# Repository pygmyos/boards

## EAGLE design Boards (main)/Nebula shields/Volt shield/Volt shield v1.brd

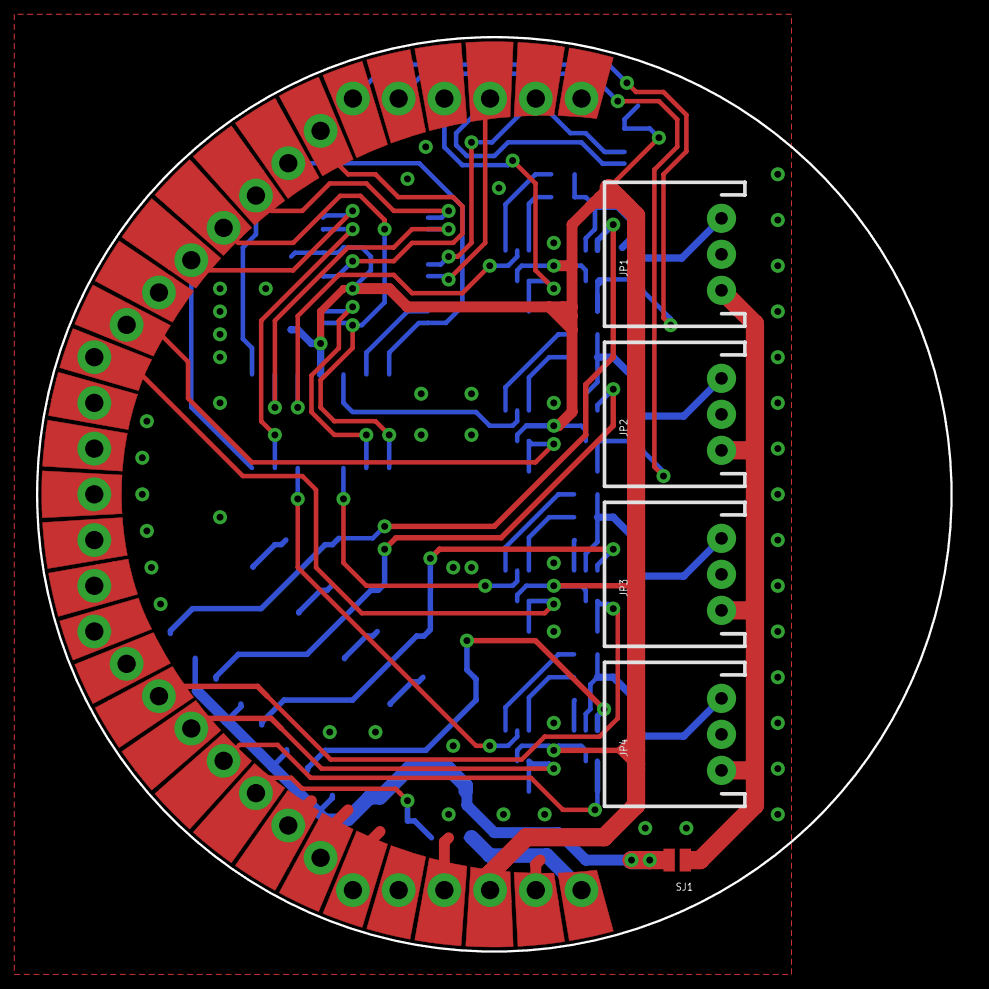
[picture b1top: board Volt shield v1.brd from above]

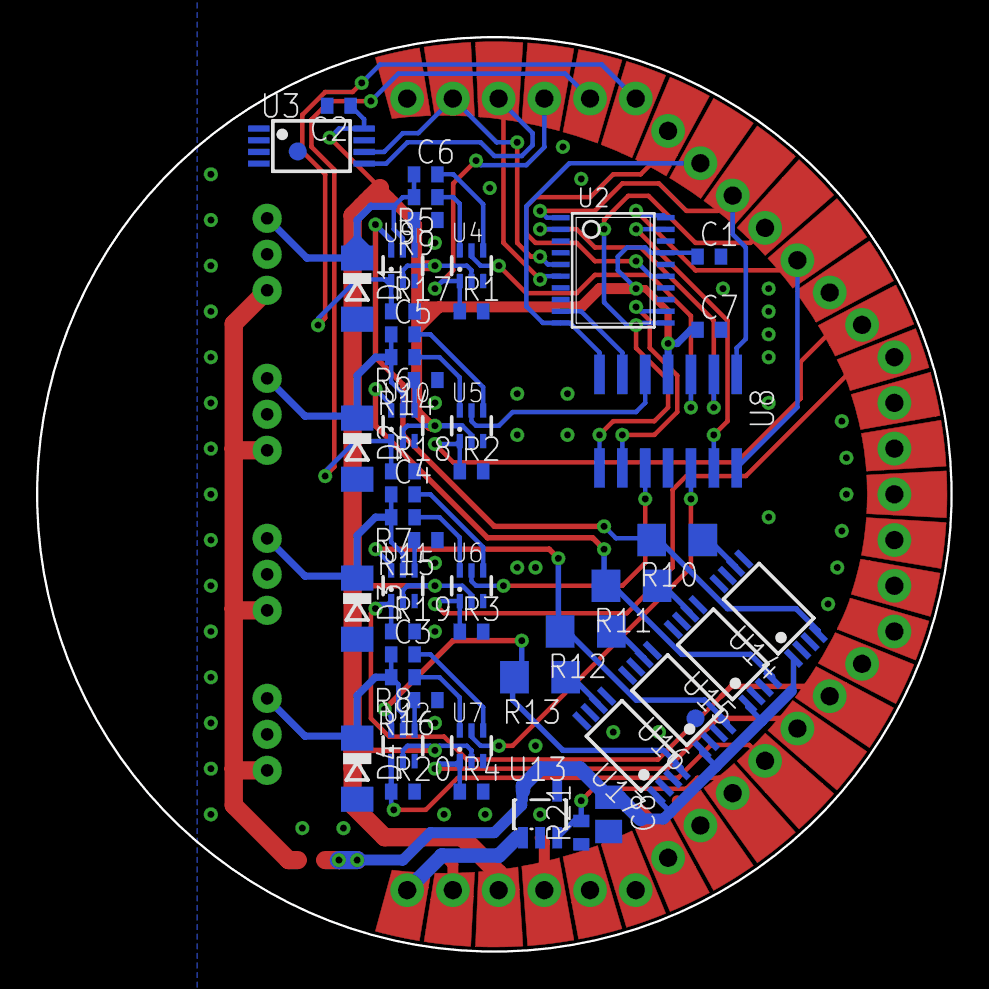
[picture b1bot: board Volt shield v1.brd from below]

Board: 2 copper layers, 50.8 x 50.8 mm, 63 parts (51 on the bottom side), 53 nets.

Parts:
C1, C2, C3, C4, C5, C6, C7: 0.1uF; C0402
C8: 10uF; C0805
D1, D2, D3, D4: 3.3V; SOD80C
INFO2: Warren D Greenway and Evan Teitelman; %CC-NC-SA
JP1, JP2, JP3, JP4: JST-3-PTH
JP5, JP6: FIDUCIAL1X2; FIDUCIAL-1X2
LOGO1: #PYGMYLOGONORMAL; #PYGMYLOGO
NEBULA1: #NEBULAPTH; #NEBULA-PTH@1
NEBULAPART1: #NEBULA-PARTRESTRICT; #NEBULA-RESTRICT
NEBULAPART2: #NEBULA-PARTLABELS-TOP; #NEBULA-LABELS-TOP
NEBULAPART3: #NEBULA-PARTCOPPER; #NEBULA-COPPER
NEBULAPART4: #NEBULA-PARTSTOP; #NEBULA-STOP
R1, R2, R3, R4, R17, R18, R19, R20, R21: 47K; R0402
R5, R6, R7, R8, R9, R14, R15, R16: 1M; R0402
R10, R11, R12, R13: 125; R1206
SJ1: SOLDERJUMPERNO; SJ_2S-NO
U2: DIGIPOT-MCP44X1; TSSOP20
U3: EEPROM-ATMEL-AT24HC02B; TSSOP8
U4, U5, U6, U7, U9, U10, U11, U12: MULTIPLEXER-TI-TS5A4624; SC70-6L
U8: OPAMP-ST-LMV324ID; SO-14
U13: NCP500; SOT23-5L
U14, U15, U16, U17: REGULATOR-TI-LM317LCPW; TSSOP8

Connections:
3.3V: C1.1, C2.1, C7.1, NEBULA1.3.3V, U2.17, U3.8, U4.2, U5.2, U6.2, U7.2, U8.4, U9.2, U10.2, U11.2, U12.2
BAT: NEBULA1.BAT, U13.1
GND: C1.2, C2.2, C7.2, C8.2, D1.A, D2.A, D3.A, D4.A, JP1.2, JP2.2, JP3.2, JP4.2, NEBULA1.GND1, NEBULA1.GND2, NEBULA1.GND3, NEBULA1.GND4, NEBULA1.GND5, R1.2, R2.2, R3.2, R4.2, R9.1, R14.1, R15.1, R16.1, R17.2, R18.2, R19.2, R20.2, R21.1, U2.3, U2.7, U2.8, U2.13, U2.18, U3.1, U3.2, U3.3, U3.4, U3.7, U4.3, U5.3, U6.3, U7.3, U8.11, U9.3, U10.3, U11.3, U12.3, U13.2
IN1: U4.5, U8.3
IN1-: U2.2, U8.2
IN2: U5.5, U8.5
IN2-: U2.9, U8.6
IN3: U6.5, U8.10
IN3-: U2.12, U8.9
IN4: U7.5, U8.12
IN4-: U2.19, U8.13
INSW1: NEBULA1.T0, R1.1, U4.1
INSW2: NEBULA1.D2, R2.1, U5.1
INSW3: NEBULA1.D1, R3.1, U6.1
INSW4: NEBULA1.TA1, R4.1, U7.1
unnamed: R5.1, U4.6
unnamed: R6.1, U5.6
unnamed: R7.1, U6.6
unnamed: R8.1, U7.6
unnamed: C3.2, U7.4
unnamed: C4.2, U6.4
unnamed: C6.1, D1.C, JP1.3, R5.2, U9.5
unnamed: JP1.1, JP2.1, JP3.1, JP4.1, SJ1.1
unnamed: C5.1, D2.C, JP2.3, R6.2, U10.5
unnamed: R10.1, U14.6
unnamed: R11.1, U15.6
unnamed: C5.2, U5.4
unnamed: C6.2, U4.4
unnamed: R12.1, U16.6
unnamed: R13.1, U17.6
unnamed: C4.1, D3.C, JP3.3, R7.2, U11.5
unnamed: R16.2, U12.4
unnamed: R15.2, U11.4
unnamed: R14.2, U10.4
unnamed: R9.2, U9.4
unnamed: C3.1, D4.C, JP4.3, R8.2, U12.5
RES1: NEBULA1.T2, R17.1, U9.1
RES2: NEBULA1.T1, R18.1, U10.1
RES3: NEBULA1.TA0, R19.1, U11.1
RES4: NEBULA1.A6, R20.1, U12.1
RESET: NEBULA1.T3, U2.15
SCL: NEBULA1.COM1_TX, U2.5, U3.6
SDA: NEBULA1.COM1_RX, U2.6, U3.5
VDD: C8.1, SJ1.2, U13.5, U14.1, U15.1, U16.1, U17.1
VENABLE: NEBULA1.A7, R21.2, U13.3
VOLT1: NEBULA1.A1, U2.1, U8.1
VOLT2: NEBULA1.A0, U2.10, U8.7
VOLT3: NEBULA1.A2, U2.11, U8.8
VOLT4: NEBULA1.A3, U2.20, U8.14
VRES1: R10.2, U9.6, U14.4
VRES2: R11.2, U10.6, U15.4
VRES3: R12.2, U11.6, U16.4
VRES4: R13.2, U12.6, U17.4

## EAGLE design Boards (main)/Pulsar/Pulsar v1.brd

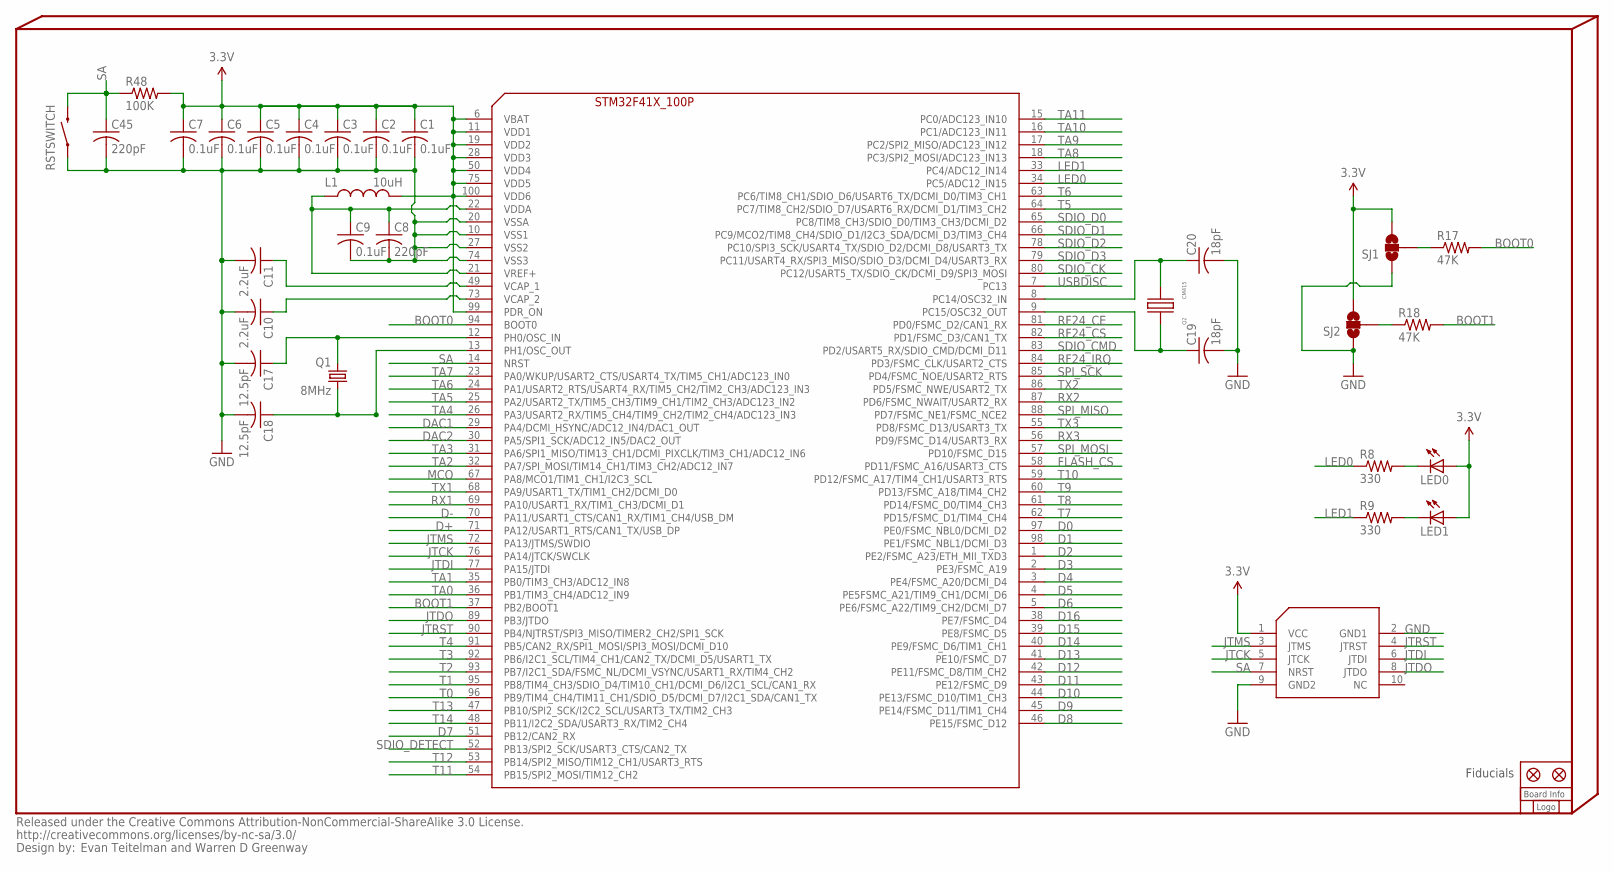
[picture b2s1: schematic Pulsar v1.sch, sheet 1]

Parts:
C1, C2, C3, C4, C5, C6, C7, C9: 0.1uF; C0402
C8, C45: 220pF; C0402
C10, C11: 2.2uF; C0402
C17, C18: 12.5pF; C0402
C19, C20: 18pF; C0402
INFO12: Evan Teitelman and Warren D Greenway; %CC-NC-SA
INFO13: %BRDINFOPULSAR; %BOARDINFO-PULSAR
JP1, JP2: FIDUCIAL1X2; FIDUCIAL-1X2
L1: 10uH; 0805
LED0, LED1: LED0603; LED-0603
LOGO1: Designed by Evan Teitelman and Warren D Greenway; #LOGOA+LONGTEXT
Q1: 8MHz; CRYSTAL-SMD-5X3
Q2: CM415
R8, R9: 330; R0402
R17, R18: 47K; R0402
R48: 100K; R0402
RSTSWITCH: SWITCH-MOMENTARY-2SMD; TACTILE_SWITCH_SMD
SJ1, SJ2: SOLDERJUMPER_2WAYS; SJ_3
U5: STM32-JTAG-10P
U$1: STM32F41X-100P; TQFP100

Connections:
3.3V: C1.1, C2.1, C3.1, C4.1, C5.1, C6.1, C7.1, L1.2, LED0.A, LED1.A, R48.2, SJ1.3, SJ2.3, U5.1 (VCC), U$1.6 (VBAT), U$1.11 (VDD1), U$1.19 (VDD2), U$1.28 (VDD3), U$1.50 (VDD4), U$1.75 (VDD5), U$1.99 (PDR_ON), U$1.100 (VDD6); also elsewhere on the board
BOOT0: R17.2, U$1.94 (BOOT0); also elsewhere on the board
BOOT1: R18.2, U$1.37 (PB2/BOOT1); also elsewhere on the board
D0: U$1.97 (PE0/FSMC_NBL0/DCMI_D2); also elsewhere on the board
D1: U$1.98 (PE1/FSMC_NBL1/DCMI_D3); also elsewhere on the board
D2: U$1.1 (PE2/FSMC_A23/ETH_MII_TXD3); also elsewhere on the board
D3: U$1.2 (PE3/FSMC_A19); also elsewhere on the board
D4: U$1.3 (PE4/FSMC_A20/DCMI_D4); also elsewhere on the board
D5: U$1.4 (PE5FSMC_A21/TIM9_CH1/DCMI_D6); also elsewhere on the board
D6: U$1.5 (PE6/FSMC_A22/TIM9_CH2/DCMI_D7); also elsewhere on the board
D7: U$1.51 (PB12/CAN2_RX); also elsewhere on the board
D8: U$1.46 (PE15/FSMC_D12); also elsewhere on the board
D9: U$1.45 (PE14/FSMC_D11/TIM1_CH4); also elsewhere on the board
D10: U$1.44 (PE13/FSMC_D10/TIM1_CH3); also elsewhere on the board
D11: U$1.43 (PE12/FSMC_D9); also elsewhere on the board
D12: U$1.42 (PE11/FSMC_D8/TIM_CH2); also elsewhere on the board
D13: U$1.41 (PE10/FSMC_D7); also elsewhere on the board
D14: U$1.40 (PE9/FSMC_D6/TIM1_CH1); also elsewhere on the board
D15: U$1.39 (PE8/FSMC_D5); also elsewhere on the board
D16: U$1.38 (PE7/FSMC_D4); also elsewhere on the board
D+: U$1.71 (PA12/USART1_RTS/CAN1_TX/USB_DP); also elsewhere on the board
D-: U$1.70 (PA11/USART1_CTS/CAN1_RX/TIM1_CH4/USB_DM); also elsewhere on the board
DAC1: U$1.29 (PA4/DCMI_HSYNC/ADC12_IN4/DAC1_OUT); also elsewhere on the board
DAC2: U$1.30 (PA5/SPI1_SCK/ADC12_IN5/DAC2_OUT); also elsewhere on the board
FLASH_CS: U$1.58 (PD11/FSMC_A16/USART3_CTS); also elsewhere on the board
GND: C1.2, C2.2, C3.2, C4.2, C5.2, C6.2, C7.2, C8.2, C9.2, C10.2, C11.2, C17.2, C18.2, C19.2, C20.2, C45.2, RSTSWITCH.1, SJ1.1, SJ2.1, U5.2 (GND1), U5.9 (GND2), U$1.10 (VSS1), U$1.20 (VSSA), U$1.27 (VSS2), U$1.74 (VSS3); also elsewhere on the board
JTCK: U5.5 (JTCK), U$1.76 (PA14/JTCK/SWCLK); also elsewhere on the board
JTDI: U5.6 (JTDI), U$1.77 (PA15/JTDI); also elsewhere on the board
JTDO: U5.8 (JTDO), U$1.89 (PB3/JTDO); also elsewhere on the board
JTMS: U5.3 (JTMS), U$1.72 (PA13/JTMS/SWDIO); also elsewhere on the board
JTRST: U5.4 (JTRST), U$1.90 (PB4/NJTRST/SPI3_MISO/TIMER2_CH2/SPI1_SCK); also elsewhere on the board
LED0: R8.1, U$1.34 (PC5/ADC12_IN15)
LED1: R9.1, U$1.33 (PC4/ADC12_IN14)
MCO: U$1.67 (PA8/MCO1/TIM1_CH1/I2C3_SCL); also elsewhere on the board
unnamed: C17.1, Q1.1, U$1.12 (PH0/OSC_IN)
unnamed: C8.1, C9.1, L1.1, U$1.21 (VREF+), U$1.22 (VDDA)
unnamed: C18.1, Q1.3 (2), U$1.13 (PH1/OSC_OUT)
unnamed: C11.1, U$1.49 (VCAP_1)
unnamed: C10.1, U$1.73 (VCAP_2)
unnamed: C20.1, Q2.P$2 (XOUT), U$1.8 (PC14/OSC32_IN)
unnamed: C19.1, Q2.P$1 (XIN), U$1.9 (PC15/OSC32_OUT)
unnamed: LED0.C, R8.2
unnamed: LED1.C, R9.2
unnamed: R17.1, SJ1.2
unnamed: R18.1, SJ2.2
RF24_CE: U$1.81 (PD0/FSMC_D2/CAN1_RX); also elsewhere on the board
RF24_CS: U$1.82 (PD1/FSMC_D3/CAN1_TX); also elsewhere on the board
RF24_IRQ: U$1.84 (PD3/FSMC_CLK/USART2_CTS); also elsewhere on the board
RX1: U$1.69 (PA10/USART1_RX/TIM1_CH3/DCMI_D1); also elsewhere on the board
RX2: U$1.87 (PD6/FSMC_NWAIT/USART2_RX); also elsewhere on the board
RX3: U$1.56 (PD9/FSMC_D14/USART3_RX); also elsewhere on the board
SA: C45.1, R48.1, RSTSWITCH.3 (2), U5.7 (NRST), U$1.14 (NRST); also elsewhere on the board
SDIO_CK: U$1.80 (PC12/USART5_TX/SDIO_CK/DCMI_D9/SPI3_MOSI); also elsewhere on the board
SDIO_CMD: U$1.83 (PD2/USART5_RX/SDIO_CMD/DCMI_D11); also elsewhere on the board
SDIO_D0: U$1.65 (PC8/TIM8_CH3/SDIO_D0/TIM3_CH3/DCMI_D2); also elsewhere on the board
SDIO_D1: U$1.66 (PC9/MCO2/TIM8_CH4/SDIO_D1/I2C3_SDA/DCMI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); also elsewhere on the board
SDIO_D2: U$1.78 (PC10/SPI3_SCK/USART4_TX/SDIO_D2/DCMI_D8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); also elsewhere on the board
SDIO_D3: U$1.79 (PC11/USART4_RX/SPI3_MISO/SDIO_D3/DCMI_D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); also elsewhere on the board
SDIO_DETECT: U$1.52 (PB13/SPI2_SCK/USART3_CTS/CAN2_TX); also elsewhere on the board
SPI_MISO: U$1.88 (PD7/FSMC_NE1/FSMC_NCE2); also elsewhere on the board
SPI_MOSI: U$1.57 (PD10/FSMC_D15); also elsewhere on the board
SPI_SCK: U$1.85 (PD4/FSMC_NOE/USART2_RTS); also elsewhere on the board
T0: U$1.96 (PB9/TIM4_CH4/TIM11_CH1/SDIO_D5/DCMI_D7/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); also elsewhere on the board
T1: U$1.95 (PB8/TIM4_CH3/SDIO_D4/TIM10_CH1/DCMI_D6/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); also elsewhere on the board
T2: U$1.93 (PB7/I2C1_SDA/FSMC_NL/DCMI_VSYNC/USART1_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); also elsewhere on the board
T3: U$1.92 (PB6/I2C1_SCL/TIM4_CH1/CAN2_TX/DCMI_D5/U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); also elsewhere on the board
T4: U$1.91 (PB5/CAN2_RX/SPI1_MOSI/SPI3_MOSI/DCMI_D10); also elsewhere on the board
T5: U$1.64 (PC7/TIM8_CH2/SDIO_D7/USART6_RX/DCMI_D1/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); also elsewhere on the board
T6: U$1.63 (PC6/TIM8_CH1/SDIO_D6/USART6_TX/DCMI_D0/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); also elsewhere on the board
T7: U$1.62 (PD15/FSMC_D1/TIM4_CH4); also elsewhere on the board
T8: U$1.61 (PD14/FSMC_D0/TIM4_CH3); also elsewhere on the board
T9: U$1.60 (PD13/FSMC_A18/TIM4_CH2); also elsewhere on the board
T10: U$1.59 (PD12/FSMC_A17/TIM4_CH1/USART3_RTS); also elsewhere on the board
T11: U$1.54 (PB15/SPI2_MOSI/TIM12_CH2); also elsewhere on the board
T12: U$1.53 (PB14/SPI2_MISO/TIM12_CH1/USART3_RTS); also elsewhere on the board
T13: U$1.47 (PB10/SPI2_SCK/I2C2_SCL/USART3_TX/TIM2_C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); also elsewhere on the board
T14: U$1.48 (PB11/I2C2_SDA/USART3_RX/TIM2_CH4); also elsewhere on the board
TA0: U$1.36 (PB1/TIM3_CH4/ADC12_IN9); also elsewhere on the board
TA1: U$1.35 (PB0/TIM3_CH3/ADC12_IN8); also elsewhere on the board
TA2: U$1.32 (PA7/SPI_MOSI/TIM14_CH1/TIM3_CH2/ADC12_I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); also elsewhere on the board
TA3: U$1.31 (PA6/SPI1_MISO/TIM13_CH1/DCMI_PIXCLK/TIM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); also elsewhere on the board
TA4: U$1.26 (PA3/USART2_RX/TIM5_CH4/TIM9_CH2/TIM2_CH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); also elsewhere on the board
TA5: U$1.25 (PA2/USART2_TX/TIM5_CH3/TIM9_CH1/TIM2_CH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); also elsewhere on the board
TA6: U$1.24 (PA1/USART2_RTS/USART4_RX/TIM5_CH2/TIM2_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); also elsewhere on the board
TA7: U$1.23 (PA0/WKUP/USART2_CTS/USART4_TX/TIM5_CH1/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); also elsewhere on the board
TA8: U$1.18 (PC3/SPI2_MOSI/ADC123_IN13); also elsewhere on the board
TA9: U$1.17 (PC2/SPI2_MISO/ADC123_IN12); also elsewhere on the board
TA10: U$1.16 (PC1/ADC123_IN11); also elsewhere on the board
TA11: U$1.15 (PC0/ADC123_IN10); also elsewhere on the board
TX1: U$1.68 (PA9/USART1_TX/TIM1_CH2/DCMI_D0); also elsewhere on the board
TX2: U$1.86 (PD5/FSMC_NWE/USART2_TX); also elsewhere on the board
TX3: U$1.55 (PD8/FSMC_D13/USART3_TX); also elsewhere on the board
USBDISC: U$1.7 (PC13); also elsewhere on the board

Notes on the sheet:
Fiducials

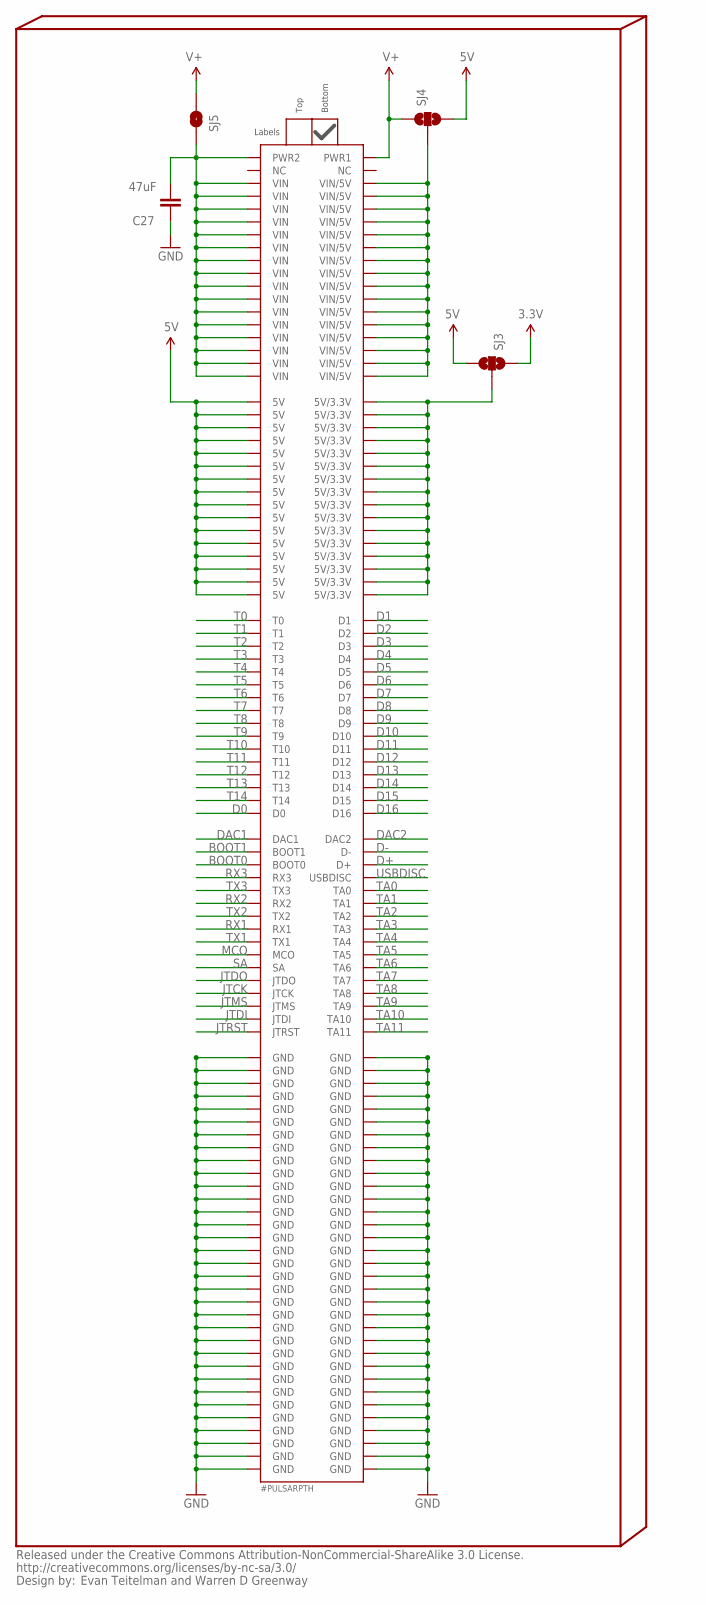
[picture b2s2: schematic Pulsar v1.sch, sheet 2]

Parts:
C27: 47uF; 1206
FP1: #PULSARPTH; #PULSAR-PTH
PULSARPART1: #PULSAR-PARTLABELS-BOTTOM; #PULSAR-LABELS-BOTT
SJ3, SJ4: SOLDERJUMPER_2WAYPASTE1&2; SJ_3_PASTE1&2
SJ5: SOLDERJUMPERNO; SJ_2S-NO

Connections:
3.3V: SJ3.1; also elsewhere on the board
5V: FP1.5V1 (5V), FP1.5V2 (5V), FP1.5V3 (5V), FP1.5V4 (5V), FP1.5V5 (5V), FP1.5V6 (5V), FP1.5V7 (5V), FP1.5V8 (5V), FP1.5V9 (5V), FP1.5V10 (5V), FP1.5V11 (5V), FP1.5V12 (5V), FP1.5V13 (5V), FP1.5V14 (5V), FP1.5V15 (5V), FP1.5V16 (5V), SJ3.3, SJ4.3; also elsewhere on the board
5V/3.3V: FP1.5V/3.3V1 (5V/3.3V), FP1.5V/3.3V2 (5V/3.3V), FP1.5V/3.3V3 (5V/3.3V), FP1.5V/3.3V4 (5V/3.3V), FP1.5V/3.3V5 (5V/3.3V), FP1.5V/3.3V6 (5V/3.3V), FP1.5V/3.3V7 (5V/3.3V), FP1.5V/3.3V8 (5V/3.3V), FP1.5V/3.3V9 (5V/3.3V), FP1.5V/3.3V10 (5V/3.3V), FP1.5V/3.3V11 (5V/3.3V), FP1.5V/3.3V12 (5V/3.3V), FP1.5V/3.3V13 (5V/3.3V), FP1.5V/3.3V14 (5V/3.3V), FP1.5V/3.3V15 (5V/3.3V), FP1.5V/3.3V16 (5V/3.3V), SJ3.2
BOOT0: FP1.BOOT0; also elsewhere on the board
BOOT1: FP1.BOOT1; also elsewhere on the board
D0: FP1.D0; also elsewhere on the board
D1: FP1.D1; also elsewhere on the board
D2: FP1.D2; also elsewhere on the board
D3: FP1.D3; also elsewhere on the board
D4: FP1.D4; also elsewhere on the board
D5: FP1.D5; also elsewhere on the board
D6: FP1.D6; also elsewhere on the board
D7: FP1.D7; also elsewhere on the board
D8: FP1.D8; also elsewhere on the board
D9: FP1.D9; also elsewhere on the board
D10: FP1.D10; also elsewhere on the board
D11: FP1.D11; also elsewhere on the board
D12: FP1.D12; also elsewhere on the board
D13: FP1.D13; also elsewhere on the board
D14: FP1.D14; also elsewhere on the board
D15: FP1.D15; also elsewhere on the board
D16: FP1.D16; also elsewhere on the board
D+: FP1.D+; also elsewhere on the board
D-: FP1.D-; also elsewhere on the board
DAC1: FP1.DAC1; also elsewhere on the board
DAC2: FP1.DAC2; also elsewhere on the board
GND: C27.2, FP1.GND1 (GND), FP1.GND2 (GND), FP1.GND3 (GND), FP1.GND4 (GND), FP1.GND5 (GND), FP1.GND6 (GND), FP1.GND7 (GND), FP1.GND8 (GND), FP1.GND9 (GND), FP1.GND10 (GND), FP1.GND11 (GND), FP1.GND12 (GND), FP1.GND13 (GND), FP1.GND14 (GND), FP1.GND15 (GND), FP1.GND16 (GND), FP1.GND17 (GND), FP1.GND18 (GND), FP1.GND19 (GND), FP1.GND20 (GND), FP1.GND21 (GND), FP1.GND22 (GND), FP1.GND23 (GND), FP1.GND24 (GND), FP1.GND25 (GND), FP1.GND26 (GND), FP1.GND27 (GND), FP1.GND28 (GND), FP1.GND29 (GND), FP1.GND30 (GND), FP1.GND31 (GND), FP1.GND32 (GND), FP1.GND33 (GND), FP1.GND34 (GND), FP1.GND35 (GND), FP1.GND36 (GND), FP1.GND37 (GND), FP1.GND38 (GND), FP1.GND39 (GND), FP1.GND40 (GND), FP1.GND41 (GND), FP1.GND42 (GND), FP1.GND43 (GND), FP1.GND44 (GND), FP1.GND45 (GND), FP1.GND46 (GND), FP1.GND47 (GND), FP1.GND48 (GND), FP1.GND49 (GND), FP1.GND50 (GND), FP1.GND51 (GND), FP1.GND52 (GND), FP1.GND53 (GND), FP1.GND54 (GND), FP1.GND55 (GND), FP1.GND56 (GND), FP1.GND57 (GND), FP1.GND58 (GND), FP1.GND59 (GND), FP1.GND60 (GND), FP1.GND61 (GND), FP1.GND62 (GND), FP1.GND63 (GND), FP1.GND64 (GND), FP1.GND65 (GND), FP1.GND66 (GND); also elsewhere on the board
JTCK: FP1.JTCK; also elsewhere on the board
JTDI: FP1.JTDI; also elsewhere on the board
JTDO: FP1.JTDO; also elsewhere on the board
JTMS: FP1.JTMS; also elsewhere on the board
JTRST: FP1.JTRST; also elsewhere on the board
MCO: FP1.MCO; also elsewhere on the board
RX1: FP1.RX1; also elsewhere on the board
RX2: FP1.RX2; also elsewhere on the board
RX3: FP1.RX3; also elsewhere on the board
SA: FP1.SA; also elsewhere on the board
T0: FP1.T0; also elsewhere on the board
T1: FP1.T1; also elsewhere on the board
T2: FP1.T2; also elsewhere on the board
T3: FP1.T3; also elsewhere on the board
T4: FP1.T4; also elsewhere on the board
T5: FP1.T5; also elsewhere on the board
T6: FP1.T6; also elsewhere on the board
T7: FP1.T7; also elsewhere on the board
T8: FP1.T8; also elsewhere on the board
T9: FP1.T9; also elsewhere on the board
T10: FP1.T10; also elsewhere on the board
T11: FP1.T11; also elsewhere on the board
T12: FP1.T12; also elsewhere on the board
T13: FP1.T13; also elsewhere on the board
T14: FP1.T14; also elsewhere on the board
TA0: FP1.TA0; also elsewhere on the board
TA1: FP1.TA1; also elsewhere on the board
TA2: FP1.TA2; also elsewhere on the board
TA3: FP1.TA3; also elsewhere on the board
TA4: FP1.TA4; also elsewhere on the board
TA5: FP1.TA5; also elsewhere on the board
TA6: FP1.TA6; also elsewhere on the board
TA7: FP1.TA7; also elsewhere on the board
TA8: FP1.TA8; also elsewhere on the board
TA9: FP1.TA9; also elsewhere on the board
TA10: FP1.TA10; also elsewhere on the board
TA11: FP1.TA11; also elsewhere on the board
TX1: FP1.TX1; also elsewhere on the board
TX2: FP1.TX2; also elsewhere on the board
TX3: FP1.TX3; also elsewhere on the board
USBDISC: FP1.USBDISC; also elsewhere on the board
V+: FP1.PWR1, SJ4.1, SJ5.2; also elsewhere on the board
VIN: C27.1, FP1.PWR2, FP1.VIN1 (VIN), FP1.VIN2 (VIN), FP1.VIN3 (VIN), FP1.VIN4 (VIN), FP1.VIN5 (VIN), FP1.VIN6 (VIN), FP1.VIN7 (VIN), FP1.VIN8 (VIN), FP1.VIN9 (VIN), FP1.VIN10 (VIN), FP1.VIN11 (VIN), FP1.VIN12 (VIN), FP1.VIN13 (VIN), FP1.VIN14 (VIN), FP1.VIN15 (VIN), FP1.VIN16 (VIN), SJ5.1
VIN/5V: FP1.VIN/5V1 (VIN/5V), FP1.VIN/5V2 (VIN/5V), FP1.VIN/5V3 (VIN/5V), FP1.VIN/5V4 (VIN/5V), FP1.VIN/5V5 (VIN/5V), FP1.VIN/5V6 (VIN/5V), FP1.VIN/5V7 (VIN/5V), FP1.VIN/5V8 (VIN/5V), FP1.VIN/5V9 (VIN/5V), FP1.VIN/5V10 (VIN/5V), FP1.VIN/5V11 (VIN/5V), FP1.VIN/5V12 (VIN/5V), FP1.VIN/5V13 (VIN/5V), FP1.VIN/5V14 (VIN/5V), FP1.VIN/5V15 (VIN/5V), FP1.VIN/5V16 (VIN/5V), SJ4.2

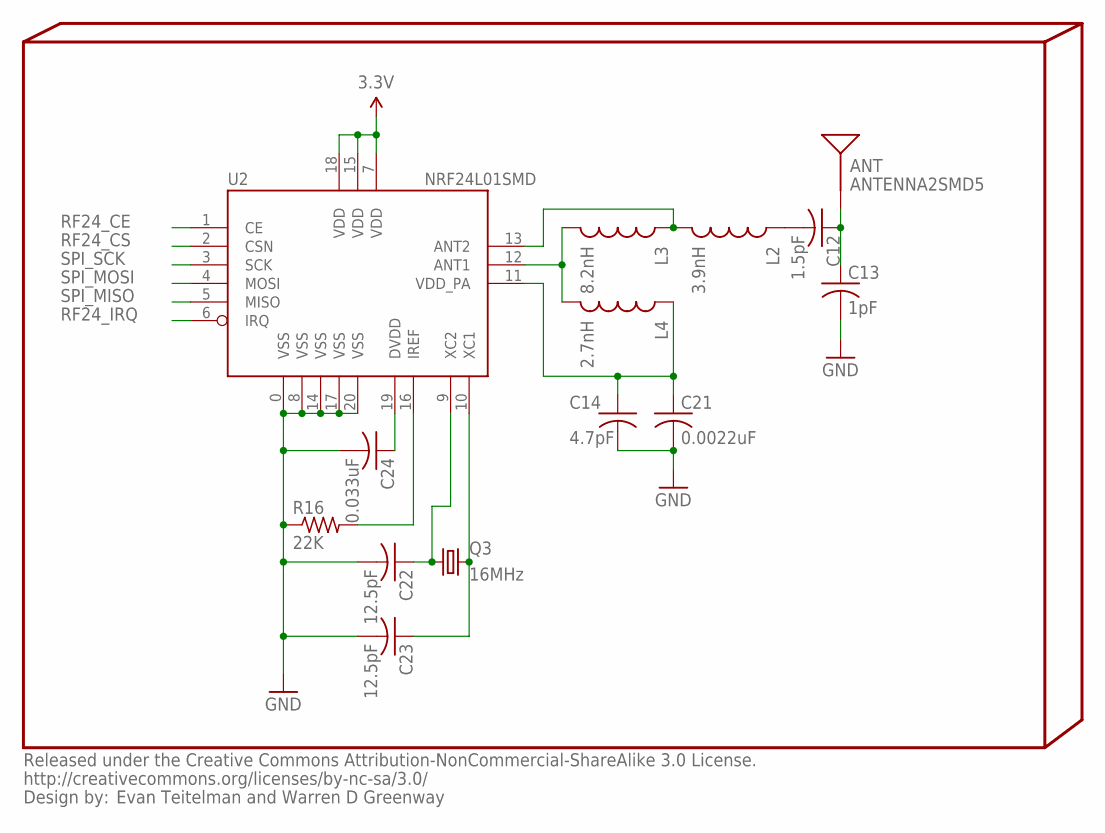
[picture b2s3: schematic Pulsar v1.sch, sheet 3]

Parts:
ANT: ANTENNA2SMD5; ANTENNA-CHIP5
C12: 1.5pF; C0402
C13: 1pF; C0402
C14: 4.7pF; C0402
C21: 0.0022uF; C0402
C22, C23: 12.5pF; C0402
C24: 0.033uF; C0402
L2: 3.9nH; 0603
L3: 8.2nH; 0603
L4: 2.7nH; 0603
Q3: 16MHz; CRYSTAL-SMD-5X3
R16: 22K; R0402
U2: NRF24L01SMD; QFN20

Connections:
3.3V: U2.7 (VDD), U2.15 (VDD), U2.18 (VDD); also elsewhere on the board
GND: C13.2, C14.2, C21.2, C22.2, C23.2, C24.2, R16.1, U2.0 (VSS), U2.8 (VSS), U2.14 (VSS), U2.17 (VSS), U2.20 (VSS); also elsewhere on the board
unnamed: C12.2, L2.1
unnamed: L3.2, L4.2, U2.12 (ANT1)
unnamed: ANT.FEED, C12.1, C13.1
unnamed: L2.2, L3.1, U2.13 (ANT2)
unnamed: C14.1, C21.1, L4.1, U2.11 (VDD_PA)
unnamed: R16.2, U2.16 (IREF)
unnamed: C24.1, U2.19 (DVDD)
unnamed: C22.1, Q3.1, U2.9 (XC2)
unnamed: C23.1, Q3.3 (2), U2.10 (XC1)
RF24_CE: U2.1 (CE); also elsewhere on the board
RF24_CS: U2.2 (CSN); also elsewhere on the board
RF24_IRQ: U2.6 (IRQ); also elsewhere on the board
SPI_MISO: U2.5 (MISO); also elsewhere on the board
SPI_MOSI: U2.4 (MOSI); also elsewhere on the board
SPI_SCK: U2.3 (SCK); also elsewhere on the board

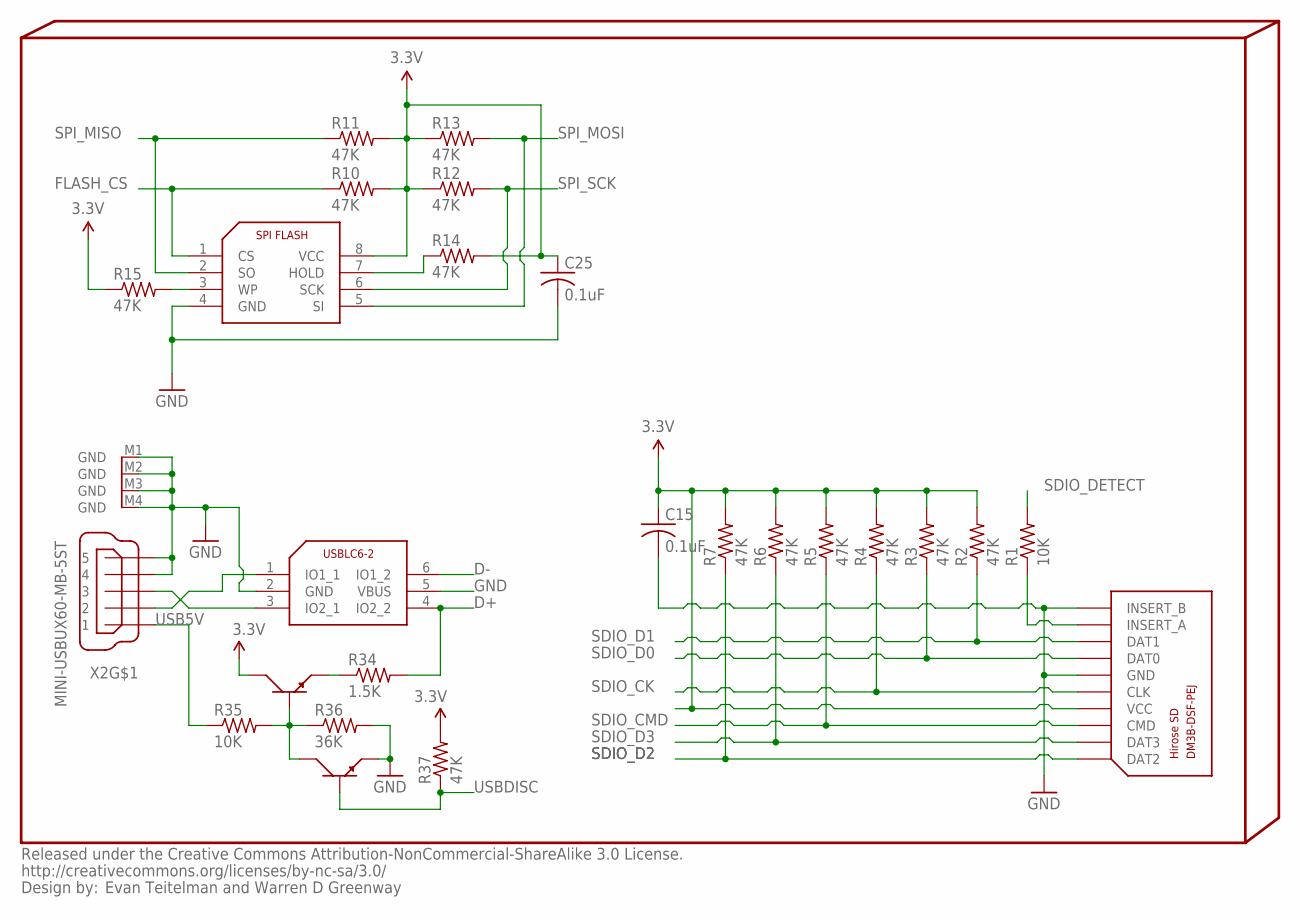
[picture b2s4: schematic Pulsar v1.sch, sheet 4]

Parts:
C15, C25: 0.1uF; C0402
R1, R35: 10K; R0402
R2, R3, R4, R5, R6, R7, R10, R11, R12, R13, R14, R15, R37: 47K; R0402
R34: 1.5K; R0402
R36: 36K; R0402
U3: SST25VF080B; DUBLIB_SOIC8
U4: USBLC6-2; SOT23-6L
U6: HIROSE-SDCARD-DM3B-DSF-PEJ
U$23, U$24: PMBT6428; SOT23
X2: MINI-USBUX60-MB-5ST; DUBLIB_UX60-MB-5ST

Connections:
3.3V: C15.1, C25.1, R2.2, R3.2, R4.2, R5.2, R6.2, R7.2, R10.2, R11.2, R12.1, R13.1, R14.2, R15.1, R37.2, U3.8 (VCC), U6.P$4 (VCC), U$23.3; also elsewhere on the board
D+: R34.2, U4.4 (IO2_2); also elsewhere on the board
D-: U4.6 (IO1_2); also elsewhere on the board
FLASH_CS: R10.1, U3.1 (CS); also elsewhere on the board
GND: C15.2, C25.2, R36.2, U3.4 (GND), U4.2 (GND), U4.5 (VBUS), U6.P$6 (GND), U6.P$11 (INSERT_B), U6.P$12 (GND), U6.P$13 (GND), U6.P$14 (GND), U$24.2, X2.4, X2.5, X2.M1 (GND), X2.M2 (GND), X2.M3 (GND), X2.M4 (GND); also elsewhere on the board
unnamed: R35.2, R36.1, U$23.1, U$24.3
unnamed: R1.1, U6.P$9 (INSERT_A)
unnamed: R34.1, U$23.2
unnamed: R15.2, U3.3 (WP)
unnamed: R14.1, U3.7 (HOLD)
unnamed: U4.1 (IO1_1), X2.2
SDIO_CK: R4.1, U6.P$5 (CLK); also elsewhere on the board
SDIO_CMD: R5.1, U6.P$3 (CMD); also elsewhere on the board
SDIO_D0: R3.1, U6.P$7 (DAT0); also elsewhere on the board
SDIO_D1: R2.1, U6.P$8 (DAT1); also elsewhere on the board
SDIO_D2: R7.1, U6.P$1 (DAT2); also elsewhere on the board
SDIO_D3: R6.1, U6.P$2 (DAT3); also elsewhere on the board
SDIO_DETECT: R1.2; also elsewhere on the board
SPI_MISO: R11.1, U3.2 (SO); also elsewhere on the board
SPI_MOSI: R13.2, U3.5 (SI); also elsewhere on the board
SPI_SCK: R12.2, U3.6 (SCK); also elsewhere on the board
USB5V: R35.1, X2.1
USBDISC: R37.1, U$24.1; also elsewhere on the board
USBP3: U4.3 (IO2_1), X2.3

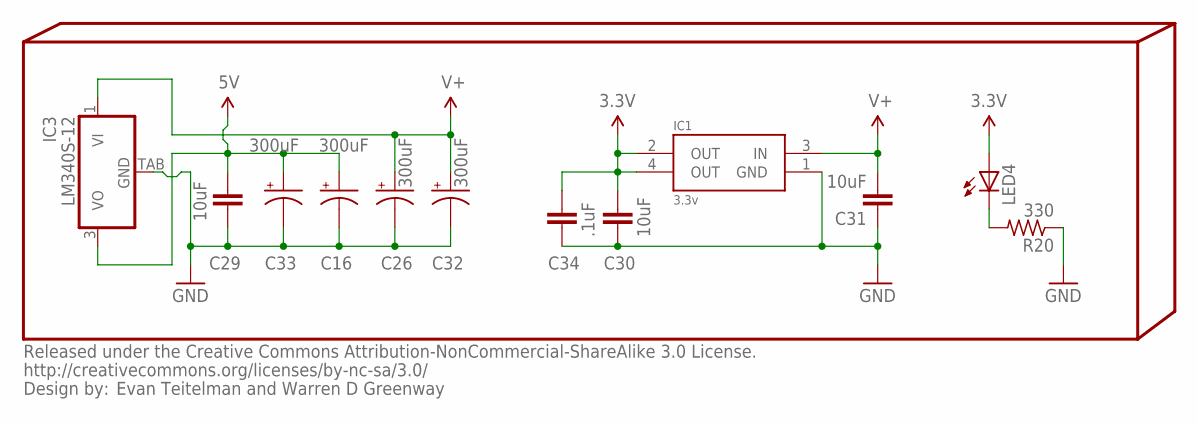
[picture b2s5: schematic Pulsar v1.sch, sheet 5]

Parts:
C16, C26, C32, C33: 300uF; PANASONIC_E
C29, C30, C31: 10uF; 1206
C34: .1uF; 0402-CAP
IC1: 3.3v; SOT223
IC3: LM340S-12; TO263-3
LED4: LED0603; LED-0603
R20: 330; R0402

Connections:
3.3V: C30.1, C34.1, IC1.2 (OUT), IC1.4 (OUT), LED4.A; also elsewhere on the board
5V: C16.+, C29.1, C33.+, IC3.3 (VO); also elsewhere on the board
GND: C16.-, C26.-, C29.2, C30.2, C31.1, C32.-, C33.-, C34.2, IC1.1 (GND), IC3.TAB (GND), R20.1; also elsewhere on the board
unnamed: LED4.C, R20.2
V+: C26.+, C31.2, C32.+, IC1.3 (IN), IC3.1 (VI); also elsewhere on the board

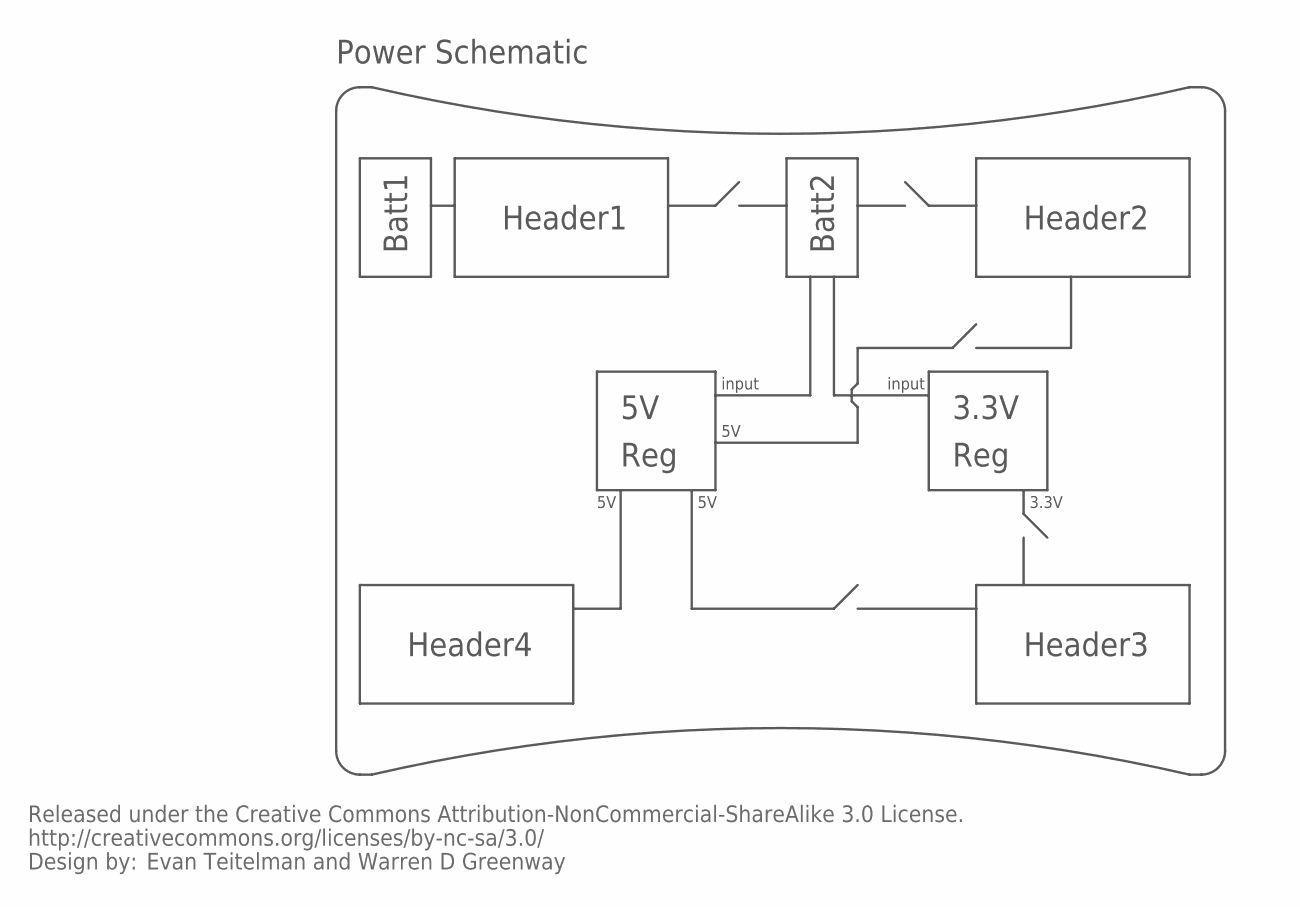
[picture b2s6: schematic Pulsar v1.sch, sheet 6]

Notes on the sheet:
Header1
Header2
Header3
Header4
Batt1
Batt2
Power Schematic
Reg
3.3V
input

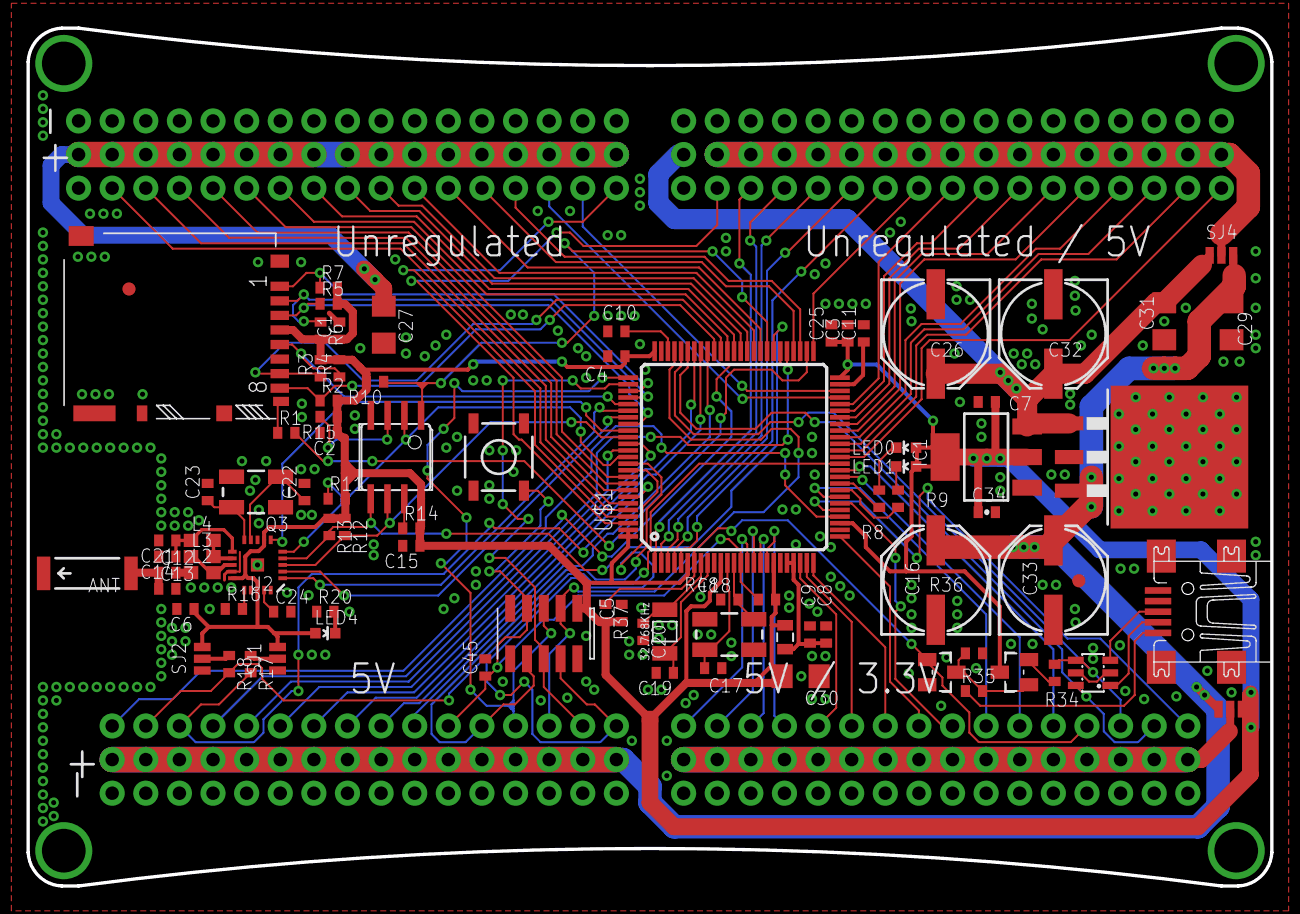
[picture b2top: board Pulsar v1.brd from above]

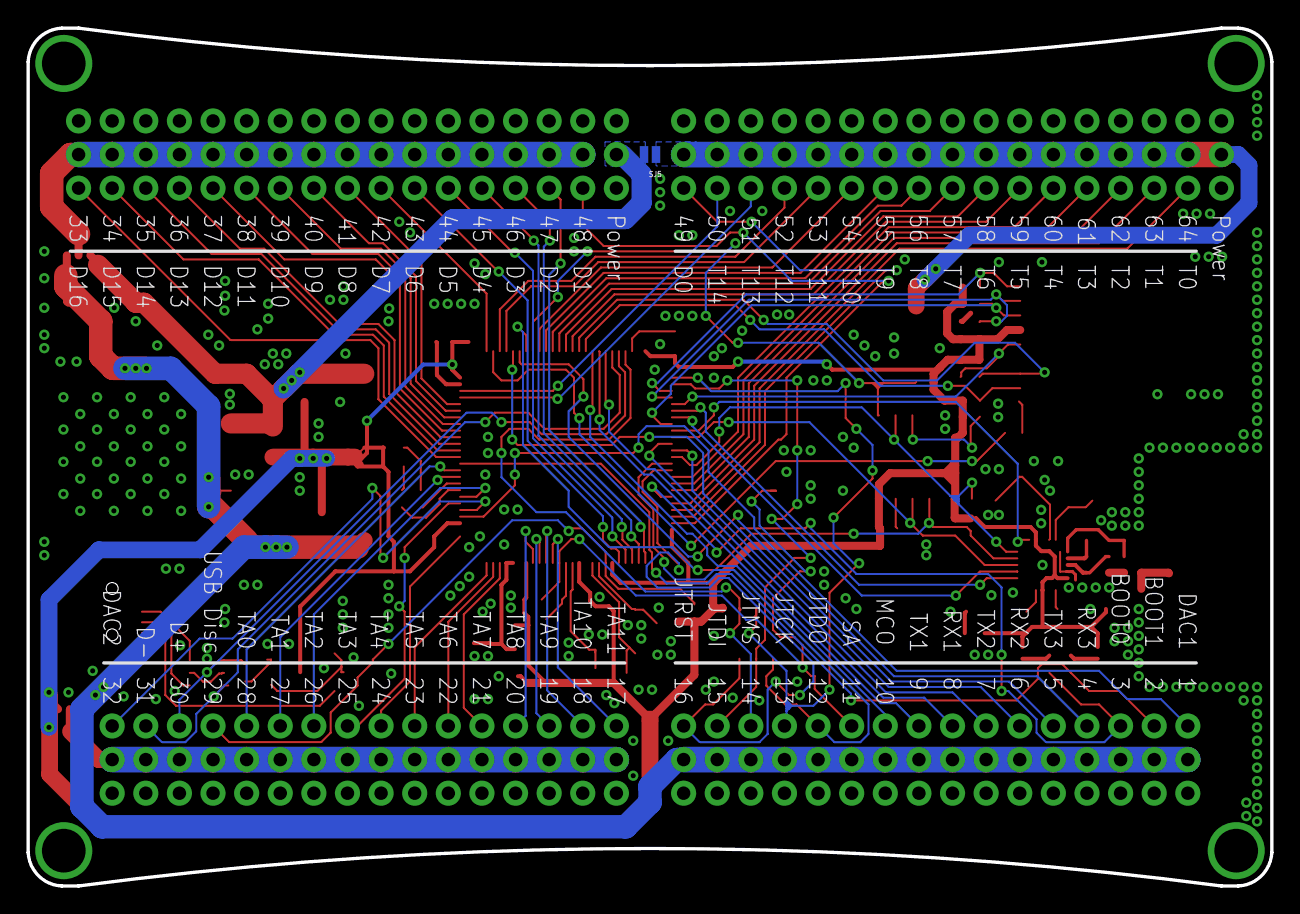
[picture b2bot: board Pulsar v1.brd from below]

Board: 2 copper layers, 94.0 x 64.8 mm, 93 parts (2 on the bottom side), 116 nets.
